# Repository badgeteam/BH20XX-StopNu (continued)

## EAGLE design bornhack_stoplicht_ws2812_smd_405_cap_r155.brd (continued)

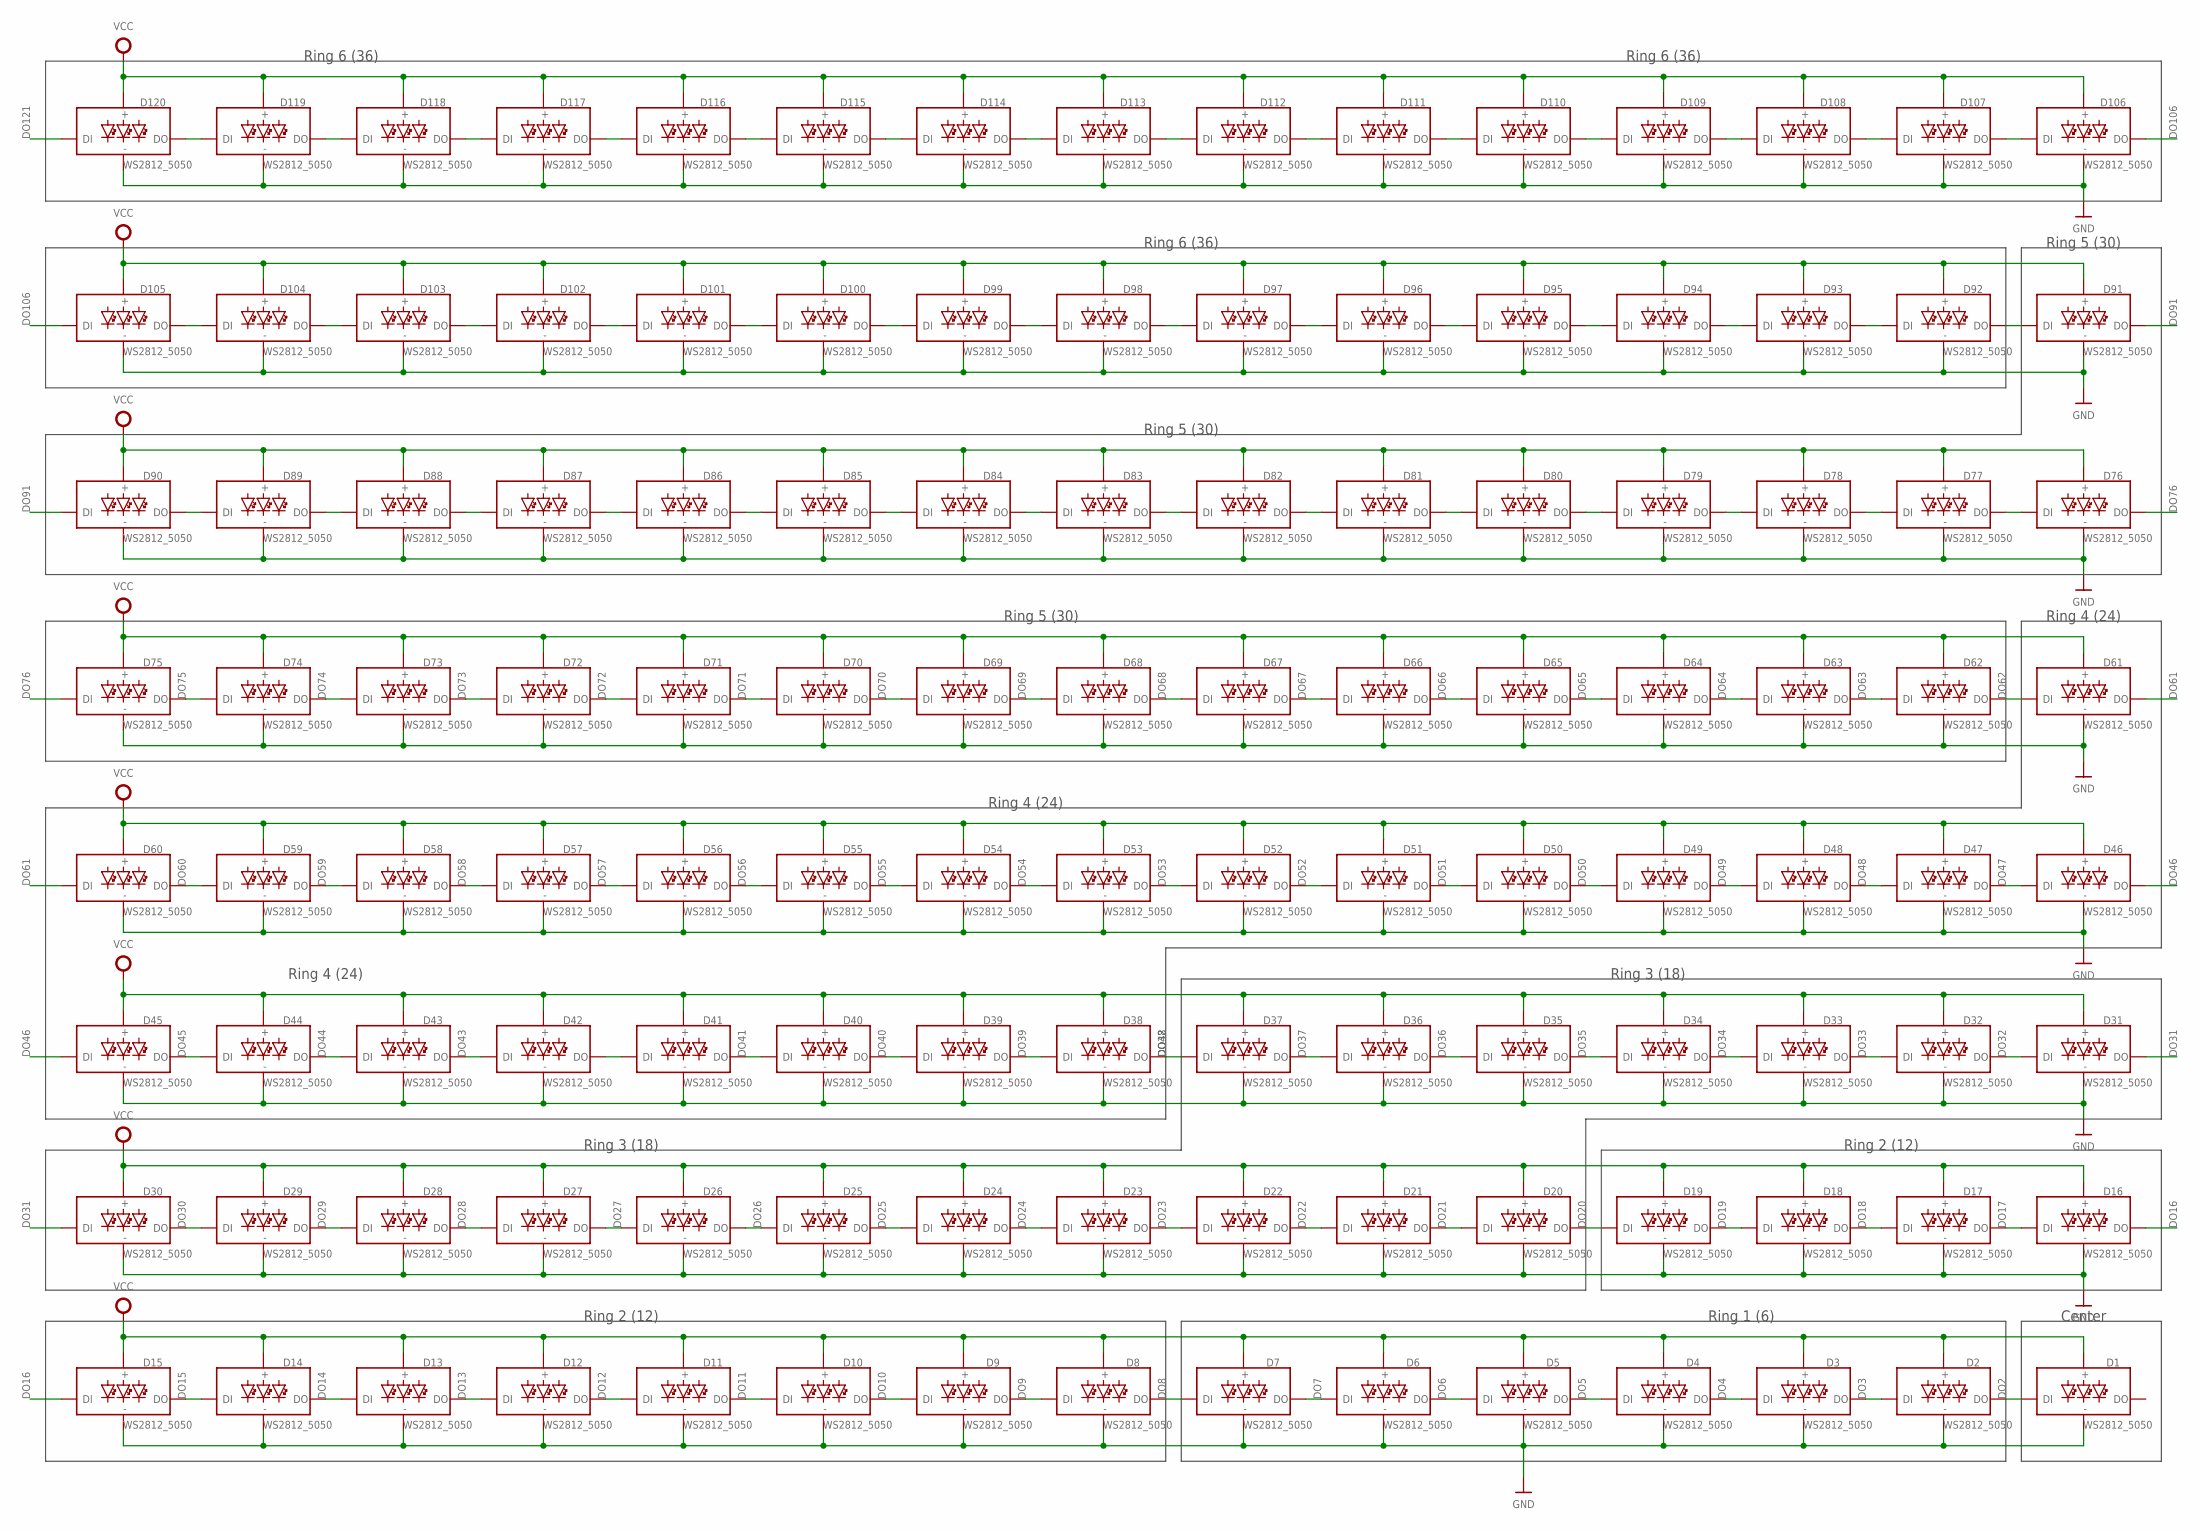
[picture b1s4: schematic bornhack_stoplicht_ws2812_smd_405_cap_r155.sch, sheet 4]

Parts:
D1, D2, D3, D4, D5, D6, D7, D8, D9, D10, D11, D12, D13, D14, D15, D16, D17, D18, D19, D20, D21, D22, D23, D24, D25, D26, D27, D28, D29, D30, D31, D32, D33, D34, D35, D36, D37, D38, D39, D40, D41, D42, D43, D44, D45, D46, D47, D48, D49, D50, D51, D52, D53, D54, D55, D56, D57, D58, D59, D60, D61, D62, D63, D64, D65, D66, D67, D68, D69, D70, D71, D72, D73, D74, D75, D76, D77, D78, D79, D80, D81, D82, D83, D84, D85, D86, D87, D88, D89, D90, D91, D92, D93, D94, D95, D96, D97, D98, D99, D100, D101, D102, D103, D104, D105, D106, D107, D108, D109, D110, D111, D112, D113, D114, D115, D116, D117, D118, D119, D120: WS2812_5050; WS2812-5X5-4PIN

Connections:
DO2: D1.DI, D2.DO
DO3: D2.DI, D3.DO
DO4: D3.DI, D4.DO
DO5: D4.DI, D5.DO
DO6: D5.DI, D6.DO
DO7: D6.DI, D7.DO
DO8: D7.DI, D8.DO
DO9: D8.DI, D9.DO
DO10: D9.DI, D10.DO
DO11: D10.DI, D11.DO
DO12: D11.DI, D12.DO
DO13: D12.DI, D13.DO
DO14: D13.DI, D14.DO
DO15: D14.DI, D15.DO
DO16: D15.DI, D16.DO
DO17: D16.DI, D17.DO
DO18: D17.DI, D18.DO
DO19: D18.DI, D19.DO
DO20: D19.DI, D20.DO
DO21: D20.DI, D21.DO
DO22: D21.DI, D22.DO
DO23: D22.DI, D23.DO
DO24: D23.DI, D24.DO
DO25: D24.DI, D25.DO
DO26: D25.DI, D26.DO
DO27: D26.DI, D27.DO
DO28: D27.DI, D28.DO
DO29: D28.DI, D29.DO
DO30: D29.DI, D30.DO
DO31: D30.DI, D31.DO
DO32: D31.DI, D32.DO
DO33: D32.DI, D33.DO
DO34: D33.DI, D34.DO
DO35: D34.DI, D35.DO
DO36: D35.DI, D36.DO
DO37: D36.DI, D37.DO
DO38: D37.DI, D38.DO
DO39: D38.DI, D39.DO
DO40: D39.DI, D40.DO
DO41: D40.DI, D41.DO
DO42: D41.DI, D42.DO
DO43: D42.DI, D43.DO
DO44: D43.DI, D44.DO
DO45: D44.DI, D45.DO
DO46: D45.DI, D46.DO
DO47: D46.DI, D47.DO
DO48: D47.DI, D48.DO
DO49: D48.DI, D49.DO
DO50: D49.DI, D50.DO
DO51: D50.DI, D51.DO
DO52: D51.DI, D52.DO
DO53: D52.DI, D53.DO
DO54: D53.DI, D54.DO
DO55: D54.DI, D55.DO
DO56: D55.DI, D56.DO
DO57: D56.DI, D57.DO
DO58: D57.DI, D58.DO
DO59: D58.DI, D59.DO
DO60: D59.DI, D60.DO
DO61: D60.DI, D61.DO
DO62: D61.DI, D62.DO
DO63: D62.DI, D63.DO
DO64: D63.DI, D64.DO
DO65: D64.DI, D65.DO
DO66: D65.DI, D66.DO
DO67: D66.DI, D67.DO
DO68: D67.DI, D68.DO
DO69: D68.DI, D69.DO
DO70: D69.DI, D70.DO
DO71: D70.DI, D71.DO
DO72: D71.DI, D72.DO
DO73: D72.DI, D73.DO
DO74: D73.DI, D74.DO
DO75: D74.DI, D75.DO
DO76: D75.DI, D76.DO
DO77: D76.DI, D77.DO
DO78: D77.DI, D78.DO
DO79: D78.DI, D79.DO
DO80: D79.DI, D80.DO
DO81: D80.DI, D81.DO
DO82: D81.DI, D82.DO
DO83: D82.DI, D83.DO
DO84: D83.DI, D84.DO
DO85: D84.DI, D85.DO
DO86: D85.DI, D86.DO
DO87: D86.DI, D87.DO
DO88: D87.DI, D88.DO
DO89: D88.DI, D89.DO
DO90: D89.DI, D90.DO
DO91: D90.DI, D91.DO
DO92: D91.DI, D92.DO
DO93: D92.DI, D93.DO
DO94: D93.DI, D94.DO
DO95: D94.DI, D95.DO
DO96: D95.DI, D96.DO
DO97: D96.DI, D97.DO
DO98: D97.DI, D98.DO
DO99: D98.DI, D99.DO
DO100: D99.DI, D100.DO
DO101: D100.DI, D101.DO
DO102: D101.DI, D102.DO
DO103: D102.DI, D103.DO
DO104: D103.DI, D104.DO
DO105: D104.DI, D105.DO
DO106: D105.DI, D106.DO
DO107: D106.DI, D107.DO
DO108: D107.DI, D108.DO
DO109: D108.DI, D109.DO
DO110: D109.DI, D110.DO
DO111: D110.DI, D111.DO
DO112: D111.DI, D112.DO
DO113: D112.DI, D113.DO
DO114: D113.DI, D114.DO
DO115: D114.DI, D115.DO
DO116: D115.DI, D116.DO
DO117: D116.DI, D117.DO
DO118: D117.DI, D118.DO
DO119: D118.DI, D119.DO
DO120: D119.DI, D120.DO
DO121: D120.DI; also elsewhere on the board
GND: D1.GND, D2.GND, D3.GND, D4.GND, D5.GND, D6.GND, D7.GND, D8.GND, D9.GND, D10.GND, D11.GND, D12.GND, D13.GND, D14.GND, D15.GND, D16.GND, D17.GND, D18.GND, D19.GND, D20.GND, D21.GND, D22.GND, D23.GND, D24.GND, D25.GND, D26.GND, D27.GND, D28.GND, D29.GND, D30.GND, D31.GND, D32.GND, D33.GND, D34.GND, D35.GND, D36.GND, D37.GND, D38.GND, D39.GND, D40.GND, D41.GND, D42.GND, D43.GND, D44.GND, D45.GND, D46.GND, D47.GND, D48.GND, D49.GND, D50.GND, D51.GND, D52.GND, D53.GND, D54.GND, D55.GND, D56.GND, D57.GND, D58.GND, D59.GND, D60.GND, D61.GND, D62.GND, D63.GND, D64.GND, D65.GND, D66.GND, D67.GND, D68.GND, D69.GND, D70.GND, D71.GND, D72.GND, D73.GND, D74.GND, D75.GND, D76.GND, D77.GND, D78.GND, D79.GND, D80.GND, D81.GND, D82.GND, D83.GND, D84.GND, D85.GND, D86.GND, D87.GND, D88.GND, D89.GND, D90.GND, D91.GND, D92.GND, D93.GND, D94.GND, D95.GND, D96.GND, D97.GND, D98.GND, D99.GND, D100.GND, D101.GND, D102.GND, D103.GND, D104.GND, D105.GND, D106.GND, D107.GND, D108.GND, D109.GND, D110.GND, D111.GND, D112.GND, D113.GND, D114.GND, D115.GND, D116.GND, D117.GND, D118.GND, D119.GND, D120.GND; also elsewhere on the board
VCC: D1.VCC, D2.VCC, D3.VCC, D4.VCC, D5.VCC, D6.VCC, D7.VCC, D8.VCC, D9.VCC, D10.VCC, D11.VCC, D12.VCC, D13.VCC, D14.VCC, D15.VCC, D16.VCC, D17.VCC, D18.VCC, D19.VCC, D20.VCC, D21.VCC, D22.VCC, D23.VCC, D24.VCC, D25.VCC, D26.VCC, D27.VCC, D28.VCC, D29.VCC, D30.VCC, D31.VCC, D32.VCC, D33.VCC, D34.VCC, D35.VCC, D36.VCC, D37.VCC, D38.VCC, D39.VCC, D40.VCC, D41.VCC, D42.VCC, D43.VCC, D44.VCC, D45.VCC, D46.VCC, D47.VCC, D48.VCC, D49.VCC, D50.VCC, D51.VCC, D52.VCC, D53.VCC, D54.VCC, D55.VCC, D56.VCC, D57.VCC, D58.VCC, D59.VCC, D60.VCC, D61.VCC, D62.VCC, D63.VCC, D64.VCC, D65.VCC, D66.VCC, D67.VCC, D68.VCC, D69.VCC, D70.VCC, D71.VCC, D72.VCC, D73.VCC, D74.VCC, D75.VCC, D76.VCC, D77.VCC, D78.VCC, D79.VCC, D80.VCC, D81.VCC, D82.VCC, D83.VCC, D84.VCC, D85.VCC, D86.VCC, D87.VCC, D88.VCC, D89.VCC, D90.VCC, D91.VCC, D92.VCC, D93.VCC, D94.VCC, D95.VCC, D96.VCC, D97.VCC, D98.VCC, D99.VCC, D100.VCC, D101.VCC, D102.VCC, D103.VCC, D104.VCC, D105.VCC, D106.VCC, D107.VCC, D108.VCC, D109.VCC, D110.VCC, D111.VCC, D112.VCC, D113.VCC, D114.VCC, D115.VCC, D116.VCC, D117.VCC, D118.VCC, D119.VCC, D120.VCC; also elsewhere on the board

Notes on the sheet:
Center
Ring 1 (6)
Ring 2 (12)
Ring 3 (18)
Ring 4 (24)
Ring 5 (30)
Ring 6 (36)

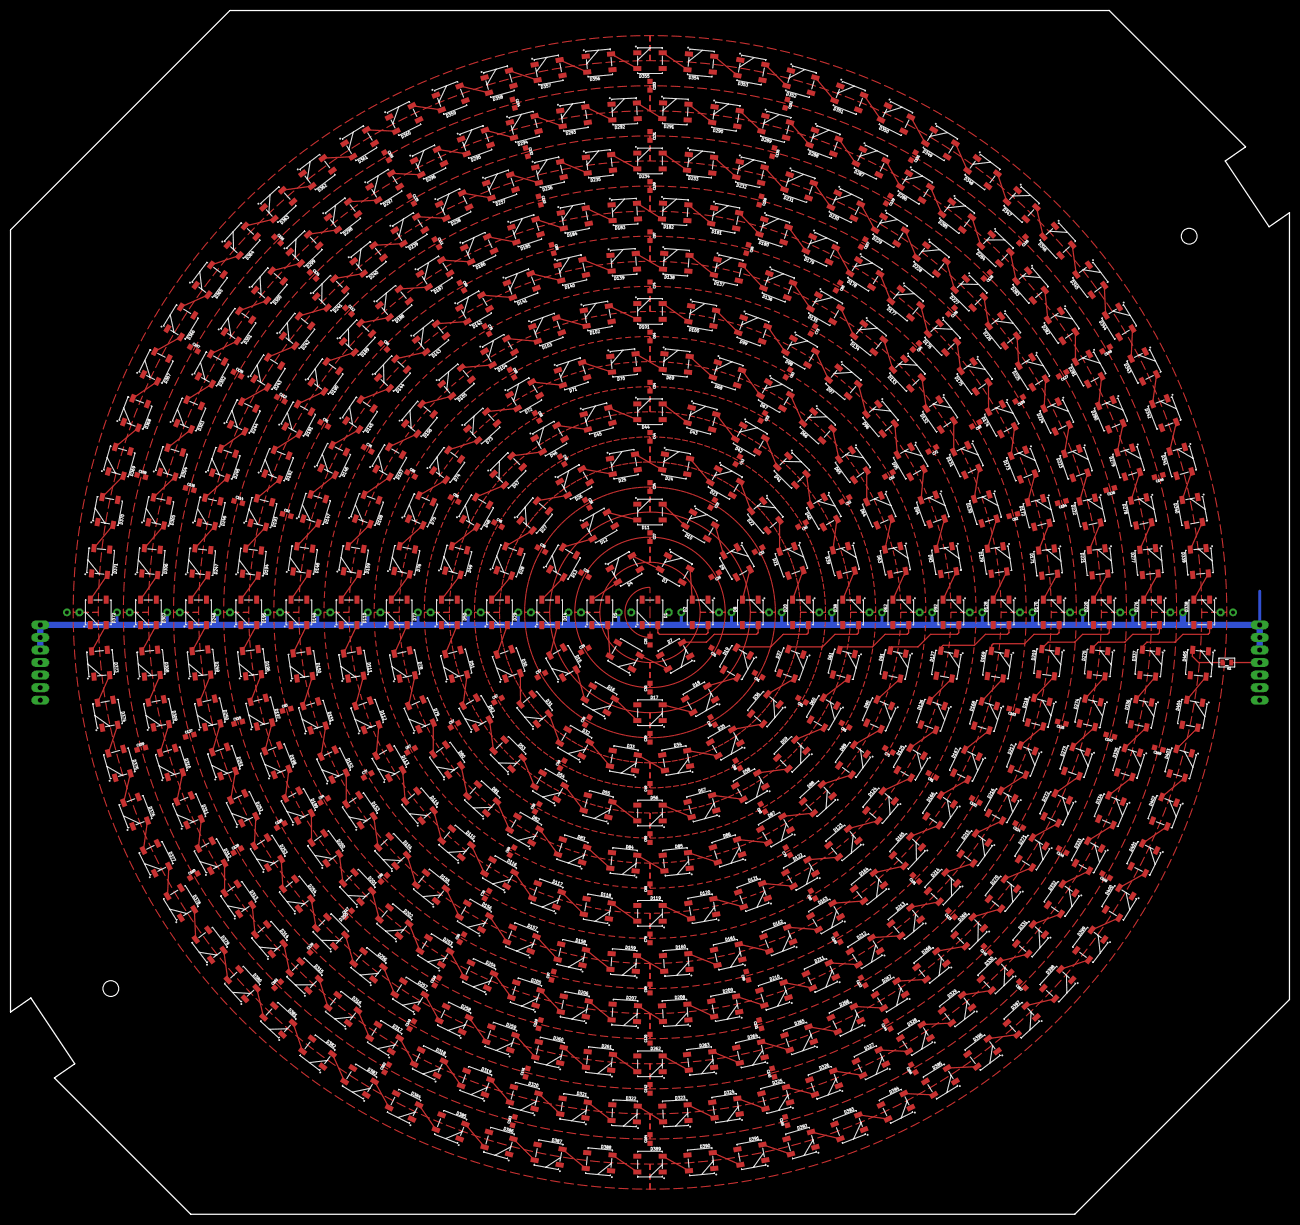
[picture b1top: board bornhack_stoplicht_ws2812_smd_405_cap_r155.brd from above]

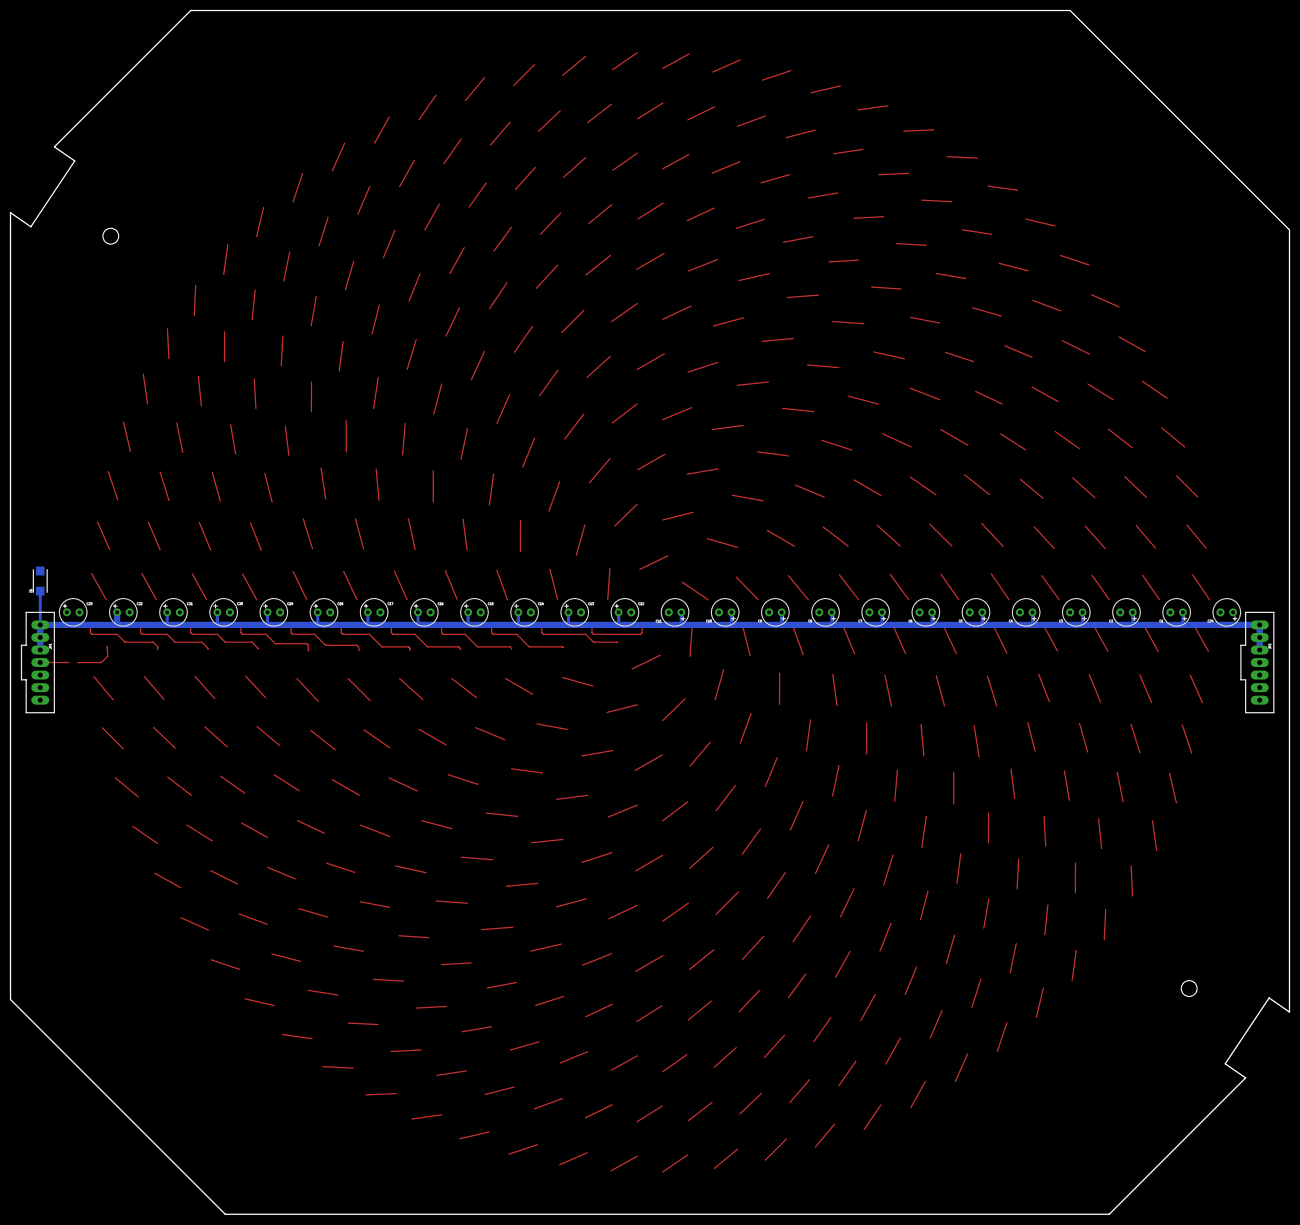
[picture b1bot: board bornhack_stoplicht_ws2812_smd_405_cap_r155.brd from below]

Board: 2 copper layers, 259.1 x 243.8 mm, 580 parts (27 on the bottom side), 408 nets.

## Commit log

2025-08-10 Create BH_traffic_control_requirements
2025-08-10 Add files via upload
    JLCPCB pick/place file
2025-08-11 Update BH_traffic_control_requirements
2025-08-11 Front window for BH traffic light
    Z dimensions as used in this drawing are irrelevant; they're only used to show the basic shapes that form the window
2025-08-31 Housing images
2025-08-31 LED panel PCB (eagle)
2025-08-31 LED panel schematic (eagle)
2025-08-31 LED panel PCB (pdf)
2025-08-31 LED panel schematic (pdf)
2025-08-31 New directory structure
2025-08-31 Moved OpenSCAD file to mechanical directory.
2025-08-31 Removed FreeCAD backup files from repository.
2025-08-31 Ignore FreeCAD backup files.
2025-09-01 OpenSCAD file to base front window design on
    Note comments, Z dimension is only indicative.
2025-09-01 Added license and README. Some cleanup.
    Added CERN Open Hardware License 2 - Permissive.
    Added README for the repository.
    Removed resulting STL file from archive.
    Updated .gitignore.
2025-09-01 Update README.md
    Typo removed.
2025-09-17 Starting with PCB mounting bracket
2025-09-17 Added mechanical drawing with dimensions for PCB bracket.
2025-09-22 Marked mounting holes that must stay accessible
2025-09-22 Revert "Marked mounting holes that must stay accessible"
    This reverts commit a7e9745887a551daacd287c190afc7d42c2e3b68.
2025-09-28 StopNu Requierements document start.
2025-09-28 fix URL.
2025-09-28 Trying to integrate issues.
2025-10-27 quick sketch
    Discord ate it
2025-12-18 Added traffic light case and assembly with PCB.
2025-12-23 Updated Stopnu vikings logo
2026-05-03 Added Lightburn file for Glasplate.
2026-05-04 Design for glassplate now done via FreeCAD.
2026-05-04 prepare PR for merge.
